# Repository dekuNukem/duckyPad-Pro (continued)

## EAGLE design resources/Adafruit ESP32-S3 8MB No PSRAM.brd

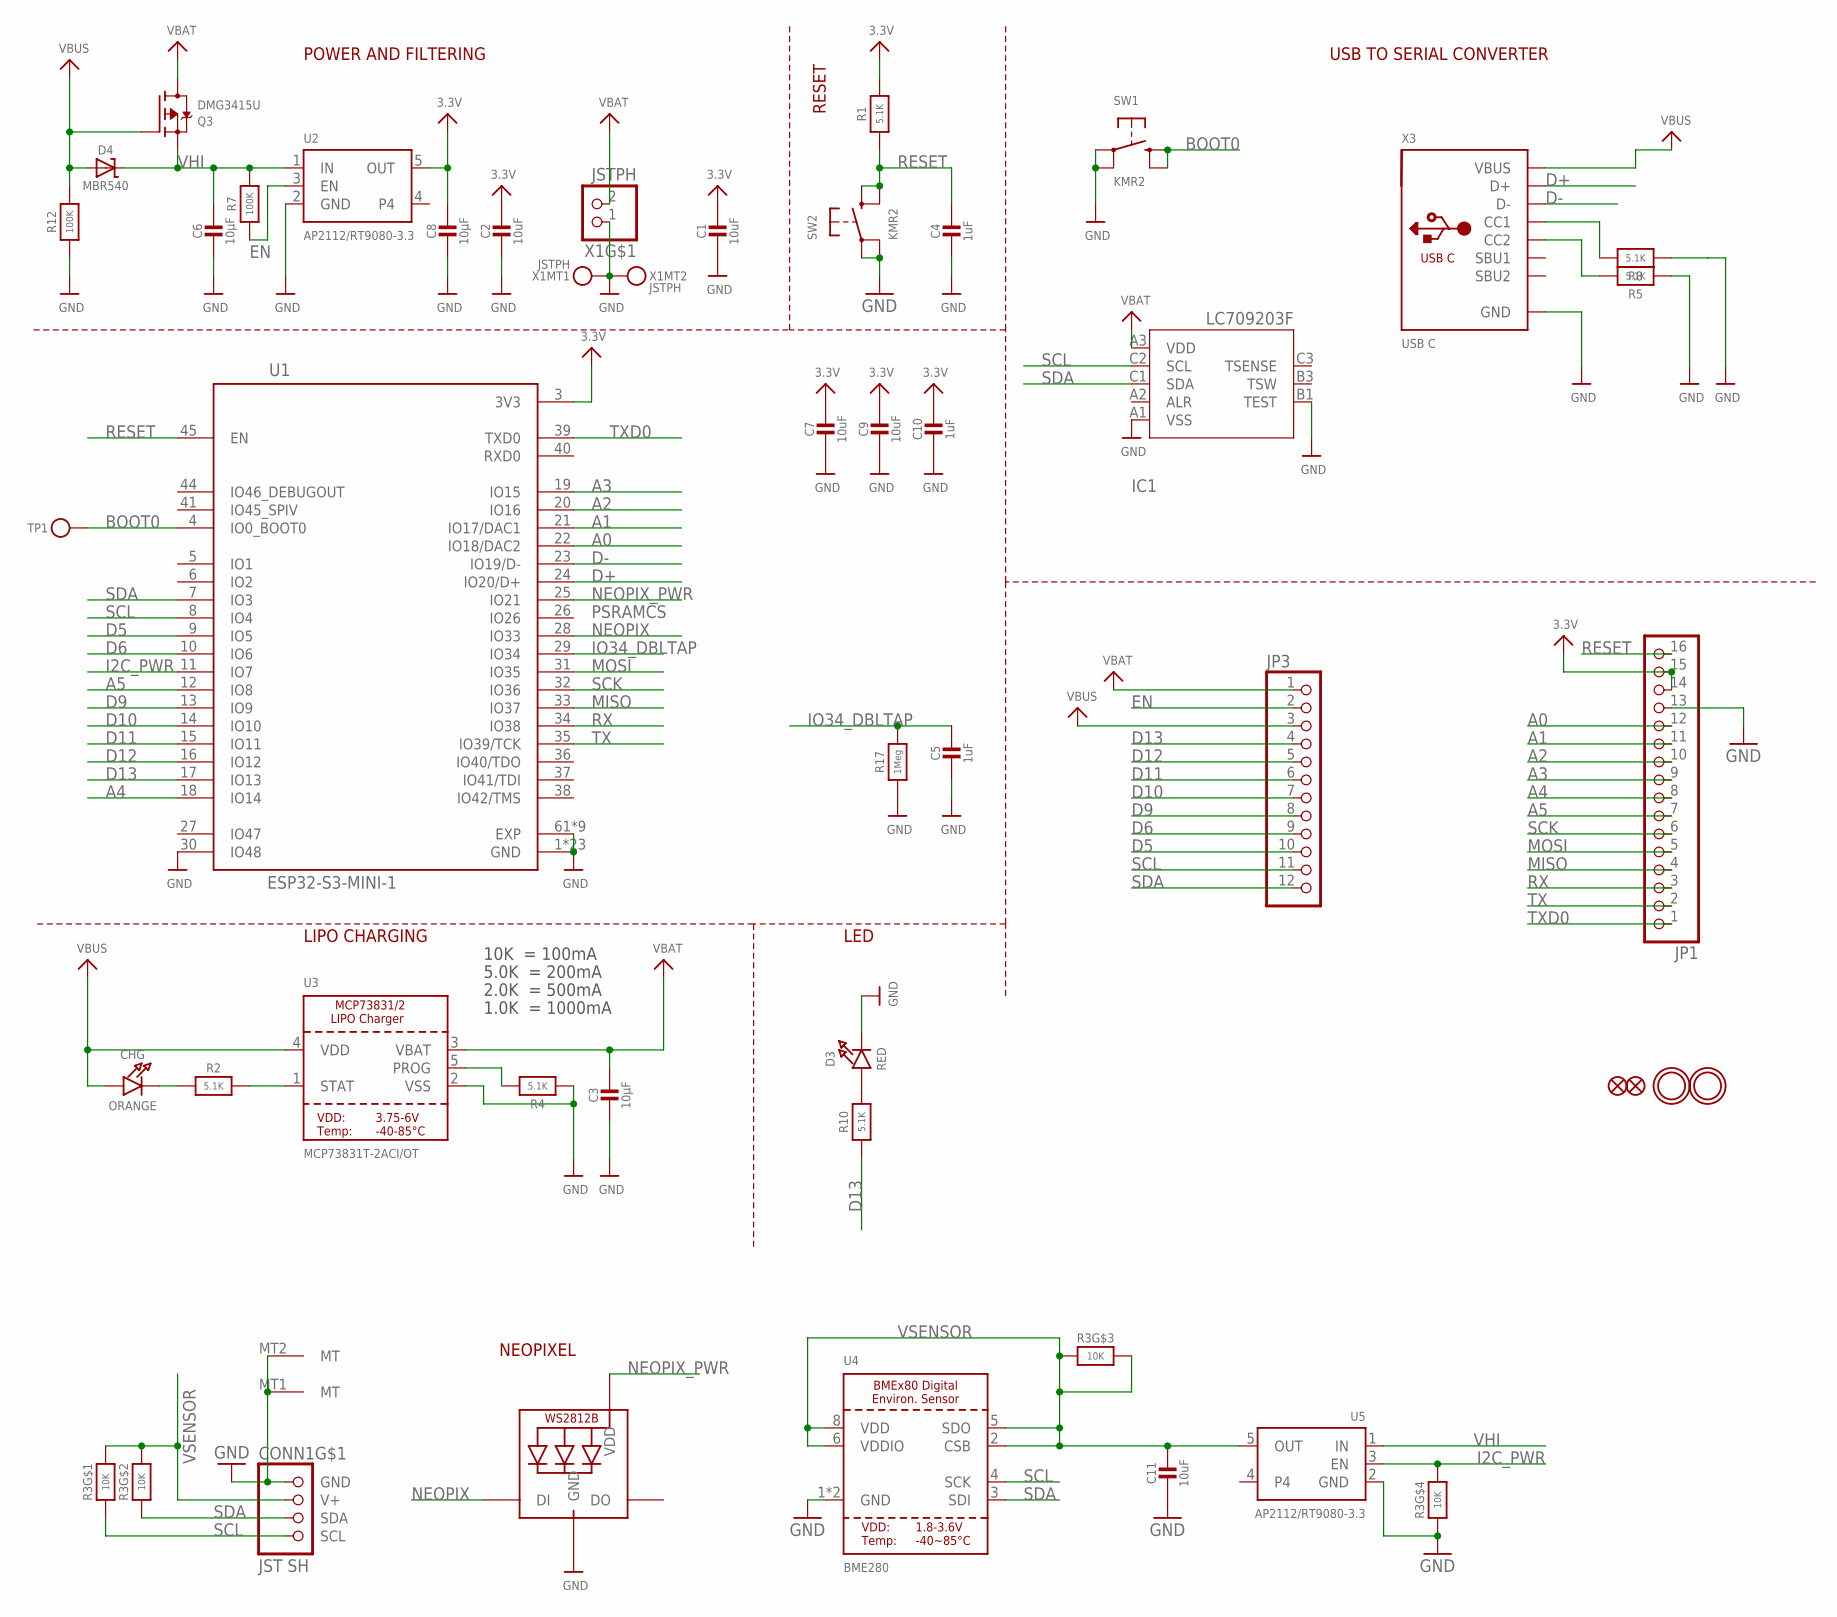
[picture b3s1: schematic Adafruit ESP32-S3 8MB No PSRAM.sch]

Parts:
C1, C2, C7, C9: 10uF; 0805-NO
C3, C6, C8: 10µF; 0805-NO
C4, C5, C10: 1uF; 0603-NO
C11: 10uF; _0805MP
CHG: ORANGE; CHIPLED_0603_NOOUTLINE
CONN1: JST SH; JST_SH4_RA
D3: RED; CHIPLED_0603_NOOUTLINE
D4: MBR540; SOD-123
IC1: LC709203F/MH; WLCSP9
JP1: HEADER-1X16ROUND; 1X16_ROUND
JP3: HEADER-1X12; 1X12_ROUND
LED1: WS2812B_SK6805_1515; SK6805_1515
Q3: DMG3415U; SOT23-R
R1, R2, R4, R5, R8, R10: 5.1K; 0603-NO
R3: 10K; RESPACK_4X0603
R7, R12: 100K; 0603-NO
R17: 1Meg; 0603-NO
SW1, SW2: KMR2; BTN_KMR2_4.6X2.8
TP1: TESTPOINTROUND1.5MMNO; TESTPOINT_ROUND_1.5MM_NO
U1: ESP32-S3-MINI-1; QFN60_ESP32-S2-MINI-1_EXP
U2, U5: AP2112/RT9080-3.3; SOT23-5
U3: MCP73831T-2ACI/OT; SOT23-5
U4: BME280
U$31, U$32: MOUNTINGHOLE2.5; MOUNTINGHOLE_2.5_PLATED
U$34, U$35: FIDUCIAL_1MM
X1: JSTPH; JSTPH2_BATT
X3: USB C; USB_C_CUSB31-CFM2AX-01-X

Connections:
3.3V: C1.1, C2.1, C7.1, C8.1, C9.1, C10.1, JP1.14, JP1.15, R1.2, U1.3 (3V3), U2.5 (OUT)
A0: JP1.12, U1.22 (IO18/DAC2)
A1: JP1.11, U1.21 (IO17/DAC1)
A2: JP1.10, U1.20 (IO16)
A3: JP1.9, U1.19 (IO15)
A4: JP1.8, U1.18 (IO14)
A5: JP1.7, U1.12 (IO8)
BOOT0: SW1.B (S), SW1.B' (S1), TP1.P$1, U1.4 (IO0_BOOT0)
D5: JP3.10, U1.9 (IO5)
D6: JP3.9, U1.10 (IO6)
D9: JP3.8, U1.13 (IO9)
D10: JP3.7, U1.14 (IO10)
D11: JP3.6, U1.15 (IO11)
D12: JP3.5, U1.16 (IO12)
D13: JP3.4, R10.1, U1.17 (IO13)
D+: U1.24 (IO20/D+), X3.A6 (D+), X3.B6 (D+)
D-: U1.23 (IO19/D-), X3.A7 (D-), X3.B7 (D-)
EN: JP3.2, R7.1, U2.3 (EN)
GND: C1.2, C2.2, C3.2, C4.2, C5.2, C6.2, C7.2, C8.2, C9.2, C10.2, C11.2, CONN1.1 (GND), CONN1.MT1 (MT), CONN1.MT2 (MT), D3.C, IC1.A1 (VSS), IC1.B1 (TEST), JP1.13, LED1.4 (GND), R3.4 (1), R4.1, R5.1, R8.1, R12.1, R17.1, SW1.A, SW1.A' (P1), SW2.A, SW2.A' (P1), U1.1 (GND), U1.2 (GND), U1.30 (IO48), U1.42 (GND), U1.43 (GND), U1.46 (GND), U1.47 (GND), U1.48 (GND), U1.49 (GND), U1.50 (GND), U1.51 (GND), U1.52 (GND), U1.53 (GND), U1.54 (GND), U1.55 (GND), U1.56 (GND), U1.57 (GND), U1.58 (GND), U1.59 (GND), U1.60 (GND), U1.61 (EXP), U1.62 (GND), U1.63 (GND), U1.64 (GND), U1.65 (GND), U1.66 (EXP), U1.67 (EXP), U1.68 (EXP), U1.69 (EXP), U1.70 (EXP), U1.71 (EXP), U1.72 (EXP), U1.73 (EXP), U2.2 (GND), U3.2 (VSS), U4.1 (GND), U4.7 (GND), U5.2 (GND), X1.1, X1.NC1, X1.NC2, X3.A1B12 (GND), X3.B1A12 (GND)
I2C_PWR: R3.5 (2), U1.11 (IO7), U5.3 (EN)
IO34_DBLTAP: C5.1, R17.2, U1.29 (IO34)
MISO: JP1.4, U1.33 (IO37)
MOSI: JP1.5, U1.31 (IO35)
unnamed: CHG.C, R2.1
unnamed: R2.2, U3.1 (STAT)
unnamed: R4.2, U3.5 (PROG)
unnamed: D3.A, R10.2
unnamed: R8.2, X3.A5 (CC1)
unnamed: R5.2, X3.B5 (CC2)
NEOPIX: LED1.1 (DI), U1.28 (IO33)
NEOPIX_PWR: LED1.2 (VDD), U1.25 (IO21)
RESET: C4.1, JP1.16, R1.1, SW2.B (S), SW2.B' (S1), U1.45 (EN)
RX: JP1.3, U1.34 (IO38)
SCK: JP1.6, U1.32 (IO36)
SCL: CONN1.4 (SCL), IC1.C2 (SCL), JP3.11, R3.1, U1.8 (IO4), U4.4 (SCK)
SDA: CONN1.3 (SDA), IC1.C1 (SDA), JP3.12, R3.2 (1), U1.7 (IO3), U4.3 (SDI)
TX: JP1.2, U1.35 (IO39/TCK)
TXD0: JP1.1, U1.39 (TXD0)
VBAT: C3.1, IC1.A3 (VDD), JP3.1, Q3.3 (D), U3.3 (VBAT), X1.2
VBUS: CHG.A, D4.A, JP3.3, Q3.1 (G), R12.2, U3.4 (VDD), X3.A4B9 (VBUS), X3.B4A9 (VBUS)
VHI: C6.1, D4.C, Q3.2 (S), R7.2, U2.1 (IN), U5.1 (IN)
VSENSOR: C11.1, CONN1.2 (V+), R3.3 (1), R3.6 (2), R3.7 (2), R3.8 (2), U4.2 (CSB), U4.5 (SDO), U4.6 (VDDIO), U4.8 (VDD), U5.5 (OUT)

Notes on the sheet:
POWER AND FILTERING
RESET
10K = 100mA
5.0K = 200mA
2.0K = 500mA
1.0K = 1000mA
USB TO SERIAL CONVERTER
LIPO CHARGING
LED
PSRAMCS
NEOPIXEL

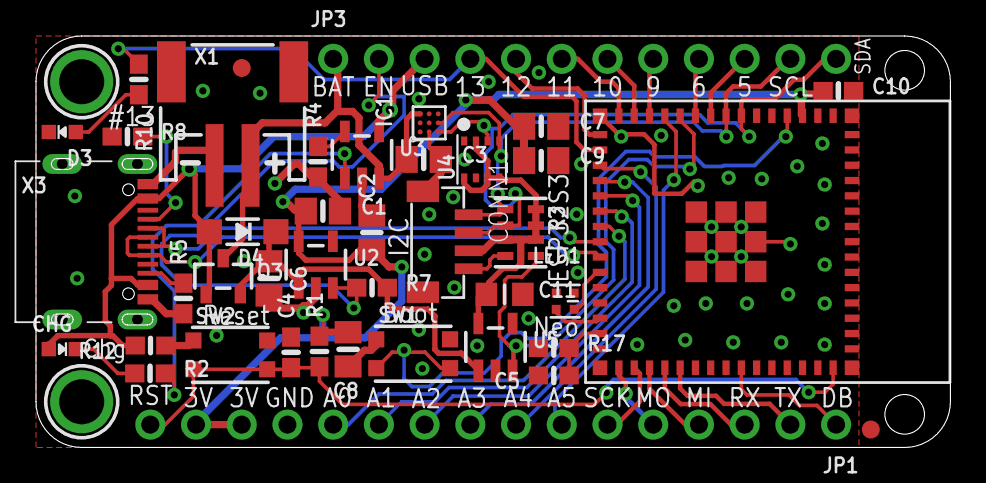
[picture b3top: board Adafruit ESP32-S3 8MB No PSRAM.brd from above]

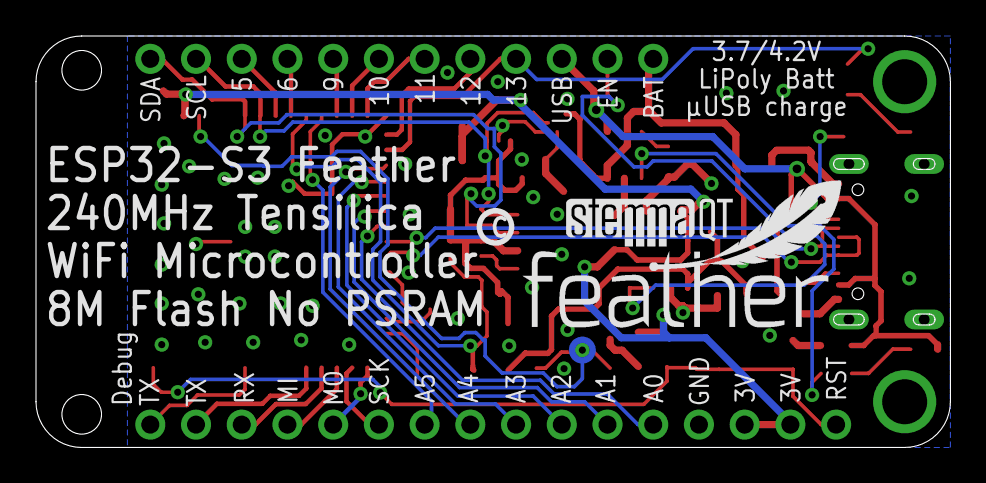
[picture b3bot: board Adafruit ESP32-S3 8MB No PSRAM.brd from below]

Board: 2 copper layers, 50.8 x 22.9 mm, 47 parts (4 on the bottom side), 42 nets.

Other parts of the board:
U$14: PCBFEAT-REV-040
U$15: FEATHERLOGO_MED
U$53: STEMMAQT

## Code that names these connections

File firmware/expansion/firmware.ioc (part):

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Mcu.Name=STM32F042F6Px
Mcu.Package=TSSOP20
Mcu.UserName=STM32F042F6Px
PA0.GPIOParameters=GPIO_Label
PA0.GPIO_Label=CH1
PA0.Signal=GPIO_Input
PA1.GPIOParameters=GPIO_Label
PA1.GPIO_Label=CH2
PA1.Signal=GPIO_Input
PA10.Mode=Asynchronous
PA10.Signal=USART1_RX
PA13.Mode=Serial_Wire
PA13.Signal=SYS_SWDIO
PA14.Mode=Serial_Wire
PA14.Signal=SYS_SWCLK
PA2.Mode=Asynchronous
PA2.Signal=USART2_TX
PA3.Mode=Asynchronous
PA3.Signal=USART2_RX
PA4.GPIOParameters=GPIO_Label
PA4.GPIO_Label=CH3
PA4.Signal=GPIO_Input
PA6.GPIOParameters=PinState,GPIO_Label
PA6.GPIO_Label=SOFTSERIAL_TX
PA6.PinState=GPIO_PIN_SET
PA6.Signal=GPIO_Output
PA7.GPIOParameters=GPIO_Label
PA7.GPIO_Label=USER_LED
PA7.Signal=GPIO_Output
PA9.Mode=Asynchronous
PA9.Signal=USART1_TX
PB1.GPIOParameters=GPIO_Label
PB1.GPIO_Label=CH4
PB1.Signal=GPIO_Input
PB8.GPIOParameters=GPIO_Label
PB8.GPIO_Label=USER_BUTTON
PB8.Signal=GPIO_Input
PF0-OSC_IN.GPIOParameters=GPIO_Label
PF0-OSC_IN.GPIO_Label=CH5
PF0-OSC_IN.Signal=GPIO_Input
PF1-OSC_OUT.GPIOParameters=GPIO_Label
PF1-OSC_OUT.GPIO_Label=CH6
PF1-OSC_OUT.Signal=GPIO_Input
RCC.SYSCLKFreq_VALUE=48000000
RCC.SYSCLKSource=RCC_SYSCLKSOURCE_HSI48
board=custom

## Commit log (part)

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2024-12-18 fixed dead key shift behaviour even more
2024-12-18 updated german keymap
2024-12-18 new firmware
2024-12-18 release new fw
2024-12-18 adjust text color for macOS dark mode
2024-12-18 macOS pyinstaller actually works wtf
2024-12-18 updated macOS build script
2024-12-19 adjusting GOTO_PROFILE parsing order
2024-12-19 made default USB MSC timeout longer
2024-12-19 updated version number
2024-12-19 now mentions DP model in backup filename
2024-12-19 updated macOS build script with onefile argument
2024-12-19 removed unused code, adjusted macOS warnings
2024-12-19 updated instruction link url and text
2024-12-20 update version change liog
2024-12-20 updated linux sudo instruction
2024-12-20 mentions expansion module in kit assembly guide
2024-12-20 update wording
2024-12-20 updated linux instruction
2024-12-20 adjust wording
2024-12-20 updated BT instruction
2024-12-20 no longer zip source at every push
2024-12-20 fixed a typo
2024-12-20 updated sample profile zip script
2024-12-20 added community showcase
2024-12-20 source zip now has version number
2024-12-21 fixed url
2024-12-24 removed standalone connectivity check
2024-12-26 added notes about UI scale
2024-12-26 updated unmount command for mac and linux
2024-12-26 clean up code
2024-12-29 moved autoswitcher macOS note to its own md
2024-12-29 updated image
2024-12-31 update sample profile
2025-01-02 reworded how to exit settings menu
2025-01-02 added more information about reserved variables
2025-01-02 more info on vmver
2025-01-06 updated push script
2025-01-06 added _DP_MODEL reserved variable
2025-01-06 added french macOS keymap
2025-01-06 adjust keypress counter increment steps
2025-01-06 update doc
2025-01-06 working on global variables
2025-01-07 working on global variable
2025-01-07 gv read write working
2025-01-07 fixed var name parsing bug
2025-01-07 global variable seems working
2025-01-08 Waking up from sleep with +/- button no longer changes profile
2025-01-09 removed test script
2025-01-09 added more instructions
2025-01-09 added README on macOS app folder
2025-01-12 clean up doc, added section about PGV
2025-01-13 fixed filename
2025-01-13 fixed DP_SLEEP bug
2025-01-13 removed unused code
2025-01-14 implementing dsl object
2025-01-14 generating dsb seems working
2025-01-14 ui key compile working
2025-01-14 more line number handling, seems to work
2025-01-15 clean file
2025-01-16 fixed links
2025-01-17 fixing address assignment but with expanded STRING commands
2025-01-17 cleanup
2025-01-31 added code screenshots
2025-01-31 updated link
2025-02-01 more details about ufl connector
2025-02-02 added kickstarter Acknowledgements
2025-02-04 updated kickstarter Acknowledgements
2025-02-06 adjust troubleshooting guide, added OLED replacement steps
2025-02-06 store link page
2025-02-06 new fw 1.1.1
2025-02-07 fix typo
2025-02-14 fixing minor bugs
2025-02-17 fixed a few warnings
2025-02-20 removed comments
2025-02-21 bug fix
2025-02-23 Assorted bugfix during backporting
2025-03-01 Add additional macOS permission requirements
    And also add some alt text to the images, never hurts.
2025-03-01 Add images of previous commit into repo.
    Instead of being left as github attachments, which would inevitably break at some point.
2025-03-01 Link to uploaded files
    And put the other two comments as their own bullet points
2025-03-03 reword
2025-03-06 Fix broken link to duckyScript docs in main README # Please enter the commit message for your changes. Lines starting # with '#' will be ignored, and an empty message aborts the commit. # # On branch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
2025-03-11 fixed a bug of settings not being saved
2025-03-11 fixed a bug where whitespace at end of KEYUP and KEYDOWN causes an syntax error
2025-03-30 working on new profile folder format conversion
2025-03-30 ok this is going to get ugly
2025-03-30 fixed bug
2025-04-04 new version number
2025-04-06 make pages build again
2025-04-10 Added udev rules for Linux
2025-04-10 moved linux instructions to its own guide
2025-04-14 fixed MOUSE_MOVE not holding mouse buttons
2025-04-21 adjusted plate cutout
2025-04-23 new fw
2025-04-24 boots into USB storage mode if SD card is emptyu
2025-04-24 removed unused files
2025-04-26 updated cheatsheet
2025-04-26 update guide
2025-05-12 adjust tolerance
2025-05-14 update link, cleanup
2025-05-23 adding caching
2025-05-23 added caching
2025-05-23 added swedish keymap by J.Laukka
2025-05-24 Reboots after changing Bluetooth mode
2025-05-24 updated linux doc
2025-05-24 update link
2025-05-24 updated ahk script to v2
2025-05-26 added notes
2025-06-14 working on half step
2025-06-14 added support for rotary encoder half-step
2025-06-14 updated screenshots
2025-06-14 fixed fw version number
2025-06-16 updated instructions
2025-06-29 adjust gv count
2025-06-29 hid gv save
2025-06-29 HID gv works while busy
2025-07-08 fixed mouse_move buffer clearance bug
2025-07-08 hopefully actually fixed it
2025-07-09 changed file name
2025-08-01 added plate gerber
2025-09-02 trying out a new HID descriptor
2025-09-03 debug msg
2025-09-03 tweaking HID descriptor
2025-09-03 removed unused bytes
2025-09-20 trying out umami
2025-09-22 updated plates
2025-09-22 added danish keymap
2025-09-25 clarification
2025-09-28 updated troubleshooting guide
2025-10-01 rebuilt fw just in case
2025-10-02 updated fw link
2025-10-03 update instructions
2025-10-05 doc cleanup
2025-11-15 new icon drawing method, working on rtc
2025-11-15 adding set_rtc hid command
2025-11-15 RTC test
2025-11-15 set RTC and valid check
2025-11-15 utc offset in minutes, in info command
2025-11-15 putting UTC offset in rtc memory, cleanup
2025-11-15 read and write to rtc variables
2025-11-15 fixed persistent state loading colors of no-longer-assigned keys
2025-11-16 added print formatting reserved variables
2025-11-16 better handling of division by zero
2025-11-16 Anykey-to-Abort now works during DELAY command
2025-11-16 Added bitwise XOR instruction in DSVM, updated dsvm doc
2025-11-16 updated doc abotu XOR
2025-11-16 No longer shows stale content on OLED on reset
2025-11-16 nevermind
2025-11-16 pcb cleanup
2025-11-18 writing doc for new commands
2025-11-18 added rtc doc, switched reserved variable doc to tables
2025-11-18 added encoder knob stl
2025-11-18 doc on RTC
2025-11-18 improved runtime error display
2025-11-18 update landing page
2025-11-19 fixed format error
2025-11-19 fixed typo
2025-11-19 updated cheatsheet, added WDAY and YDAY
2025-11-19 added beta fw
2025-11-20 added links
2025-11-23 start working on DSVM V2, adding new address def
2025-11-23 modifying address
2025-11-23 porting to 32 bit
2025-11-23 porting to 32 bit, seems working?
2025-11-23 fixed wrong interger casting, pong works
2025-11-26 working on doc
2025-11-26 added new fw
2025-11-26 new fw live
2025-12-06 preparing for next run
2025-12-15 new revision adjustment
2025-12-16 1000Hz polling rate
2025-12-16 added notes
2025-12-18 start porting new vm
2025-12-18 new vm compiles, not finished yet
2025-12-18 dsvm2 dry run works
2025-12-19 added back dsb cache
2025-12-20 moved curr_pc inside exe context
2025-12-20 fixed div by zero in rng, pong works
2025-12-20 implemented new GOTO_PROFILE logic, seems working, more testing needed
2025-12-21 added sw bitfield
2025-12-21 added sw_color_user_assigned, changed names, added has_custom_colors
2025-12-21 adjusted name, added to changelog
2025-12-21 fixed a bug related to max profile name length
2025-12-22 new sps load and save, snprintf, loopsize fix
2025-12-22 new redraw_bg function, user defined led color seems working
2025-12-22 code cleanup
2025-12-22 updated sample profiles
2025-12-22 updated duckyscript docs
2025-12-23 working on new update doc
2025-12-24 writing draft
2025-12-24 writing update page
2025-12-24 writing doc, adjusted top plate gap
2025-12-25 update notes deeper dive
2025-12-25 text cleanup
2025-12-26 added PEEK8, POKE8, and scratch memory area
2025-12-26 Added PUSH0 and DROP instruction
2025-12-27 adjusted silkscreen
2025-12-30 updated silkscreen
2025-12-30 adjust silkscreen
2025-12-30 porting over vm, mostly working
2025-12-30 randchr and puts seems working
2025-12-31 writing changelog
2025-12-31 updating links, cleanup
2025-12-31 added reserved bytes padding and removed motion wakeup in hid descriptor
2025-12-31 added horizontal scrolling to HID descriptor, seems working
2026-01-01 clean up hid descriptor
2026-01-01 updated mouse scroll commands
2026-01-01 added PUSH8, adjusted MSCL, cleanup
2026-01-01 clarify defaultdelay and defaultchardelay behaviors, doc cleanup
2026-01-01 6 key rollover
2026-01-01 mentioned new features in update doc
2026-01-01 adjust BT hid descriptor to support 6KRO and horizontal scrolling
2026-01-01 streamlined hid send function
2026-01-01 added forward and backward button on mouse, added more media keys, fixed scroll release bug
2026-01-01 hidrtx seems work
2026-01-01 new toc maker, renamed HIDTX
2026-01-01 doc clean
2026-01-06 working on docs
2026-01-06 updated cheatsheet
2026-01-06 doc cleanup, wrote more about BCLR command
2026-01-09 new toc
2026-01-10 support oled centered print, added subl syntax highlighter
2026-01-10 syntax highlighter good enough
2026-01-10 support for function and end_function
2026-01-11 reword changelog
2026-01-11 added GUI key in guide
2026-01-11 18 char per line
2026-01-11 new cheatsheet
2026-01-11 new OLED_PRINT instruction format, new version number, cleanup
2026-01-12 updaing doc
2026-01-12 explicit unsigned functions, info about poke and peek
2026-01-12 working on randuint
2026-01-14 updated changelog
2026-01-14 updated changelog with latest changes
2026-01-15 added PASS command
2026-01-15 port over peek poke unsigned ops and reserved var cleanup
2026-01-15 adjusted PUTS and RANDCHR bitfield
2026-01-15 remove unused code
2026-01-16 added notes about char declaration
2026-01-17 new pgv read and write HID command in little endian
2026-01-17 updated hid rtc command
2026-01-17 oled shape draw options
2026-01-18 fixed off by 1
2026-01-19 preparing beta test
2026-01-20 switched to strncpy
2026-01-21 use hardware RNG in randchr, adjust oled circle clamp
2026-01-21 simpler cache check
2026-01-22 updated doc
2026-01-26 fixed _THIS_KEYID off-by-1 bug
2026-01-26 OLED drawing optimisation
2026-01-26 cleanup flappy bird code
2026-01-26 adjusted usb callback
2026-01-28 new fw and docs
2026-02-09 preparing for public release
2026-02-09 fix link
2026-02-10 added a cleaned up doc for ai
2026-02-13 updated sample profile for new update
2026-02-16 updated pcb files
2026-02-16 new side push button
2026-02-16 new bottom plate silkscreen
2026-02-16 updated sw_bitfield description
2026-03-11 inverted default PWM level to reduce power consumption
2026-03-15 Increased Anykey-to-Abort check frequency
2026-03-15 cleanup doc
2026-03-17 added notes on ai help
2026-03-22 concurrent script copy
2026-04-10 fixed typos
2026-06-04 Add HID command protocol for PC-driven mouse control
    Introduce four new HID command packet IDs on the custom command
    interface (Report ID 5) so the mouse can be controlled entirely from
    the PC over USB, without depending on physical buttons or DuckyScript:
    - HID_COMMAND_MOUSE_MOVE_DELTA (0x05): relative move by signed x/y
    - HID_COMMAND_MOUSE_MOVE_STATIC (0x06): absolute move-to-position
    - HID_COMMAND_MOUSE_CLICK (0x07): press/hold button(s)
